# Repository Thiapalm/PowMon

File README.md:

# (PowMon) Power Monitor Board

<p align=center>

</p>

This is a hobby development board conceived for usage in my home lab. The device monitors both a shunt  voltage drop and bus supply voltage. Programmable calibration value, conversion times, and averaging,  combined with an internal multiplier, enable direct readouts of current in amperes and power in watts.

The board has 2 headers used for address configuration, allowing all 16 addresses to be used as you see fit. The board power is provided by the I²C connector, and it can be used in 5V or 3V3 modes. 

## License and certification

This is an open source hardware project licensed under CERN-OHL-P. More details on [LICENSE.md](./LICENSE.md).  

## Project

The PCB project was developed in Kicad 9, all necessary project files are available in this repository and can be used freely, according to License.

## Board specifications

The board is based on the [**INA226**](https://www.ti.com/lit/gpn/ina226) from Texas Instruments.  
Board features commonly used in Embedded Systems:
- Measure voltages from 0V up to 36V
- Configurable averaging options
- Reports current, voltage and power
- I²C serial communication (Two Headers for BUS usage)
- LED indicators (LOAD, Board POWER and ALERT)
- 2.7v up to 5v operation voltage from I²C header
- Board Address selector (A0 and A1)

## Board View 

## Board Enclosure 

There is an enclosure made in Freecad 1.0 available on the enclosure folder, it can be used or modified as you see fit. For best results I recommend to print in transparent filament. You will also need 4 M3 x 10mm screws (black with flat head are recommended).  

## Version Revision

V1 - current version  
   - Added two I²C headers so it can be used in a bus
   - Added Address configuration headers
   - Added informational LEDs

## Firmware

There is no specific firmware for this board, but i have a driver (crate) developed in RUST for INA226, see it in [crates.io](https://crates.io/crates/ina226-tp) or you can search the internet for a c/c++ version.

## Contribution

Unless you explicitly state otherwise, any contribution intentionally submitted for inclusion in the work by you, as defined in the CERN-OHL-P license, shall be licensed as above, without any additional terms or conditions.

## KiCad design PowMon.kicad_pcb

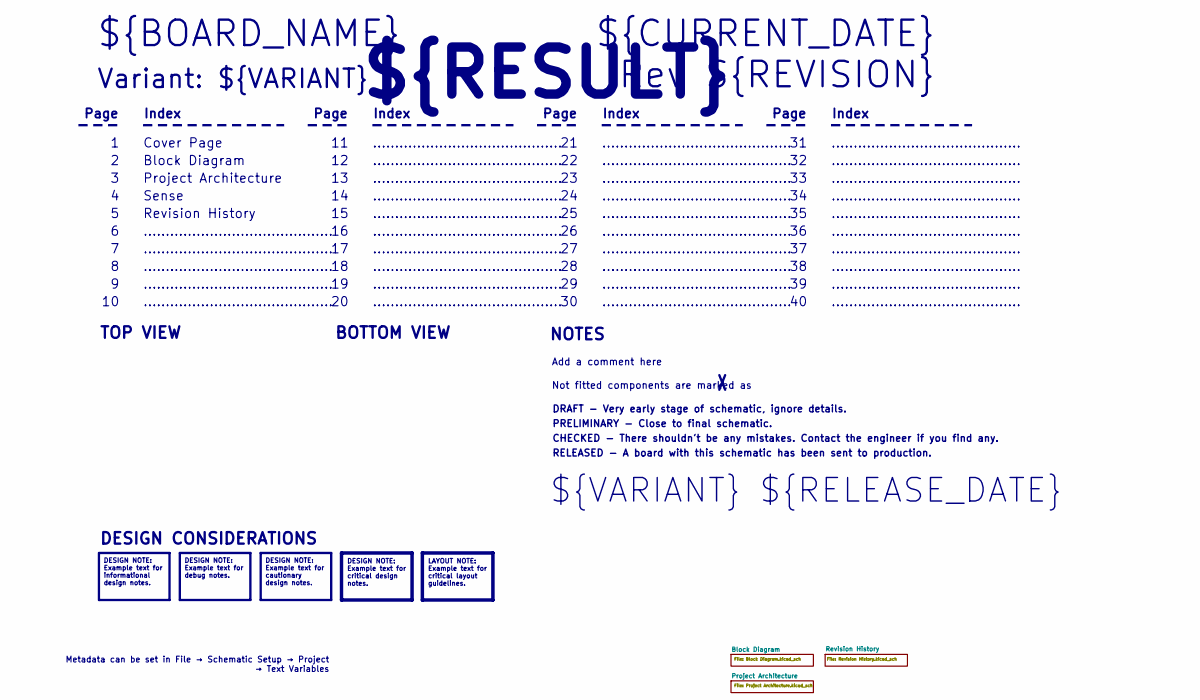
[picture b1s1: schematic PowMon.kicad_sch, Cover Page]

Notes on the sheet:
BOTTOM VIEW
...........................................
RELEASED - A board with this schematic has been sent to production.
Page
TOP VIEW
Not fitted components are marked as
Index
PRELIMINARY - Close to final schematic.
${VARIANT} ${RELEASE_DATE}
Sense
${CURRENT_DATE}
Variant: ${VARIANT}
Rev ${REVISION}
Revision History
${RESULT}
${BOARD_NAME}
DRAFT - Very early stage of schematic, ignore details.
Block Diagram
Add a comment here
Cover Page
NOTES
Project Architecture
CHECKED - There shouldn't be any mistakes. Contact the engineer if you find any.
DESIGN CONSIDERATIONS
Metadata can be set in File → Schematic Setup → Project → Text Variables
DESIGN NOTE: Example text for informational design notes.
LAYOUT NOTE: Example text for critical layout guidelines.
DESIGN NOTE: Example text for cautionary design notes.
DESIGN NOTE: Example text for debug notes.
DESIGN NOTE: Example text for critical design notes.

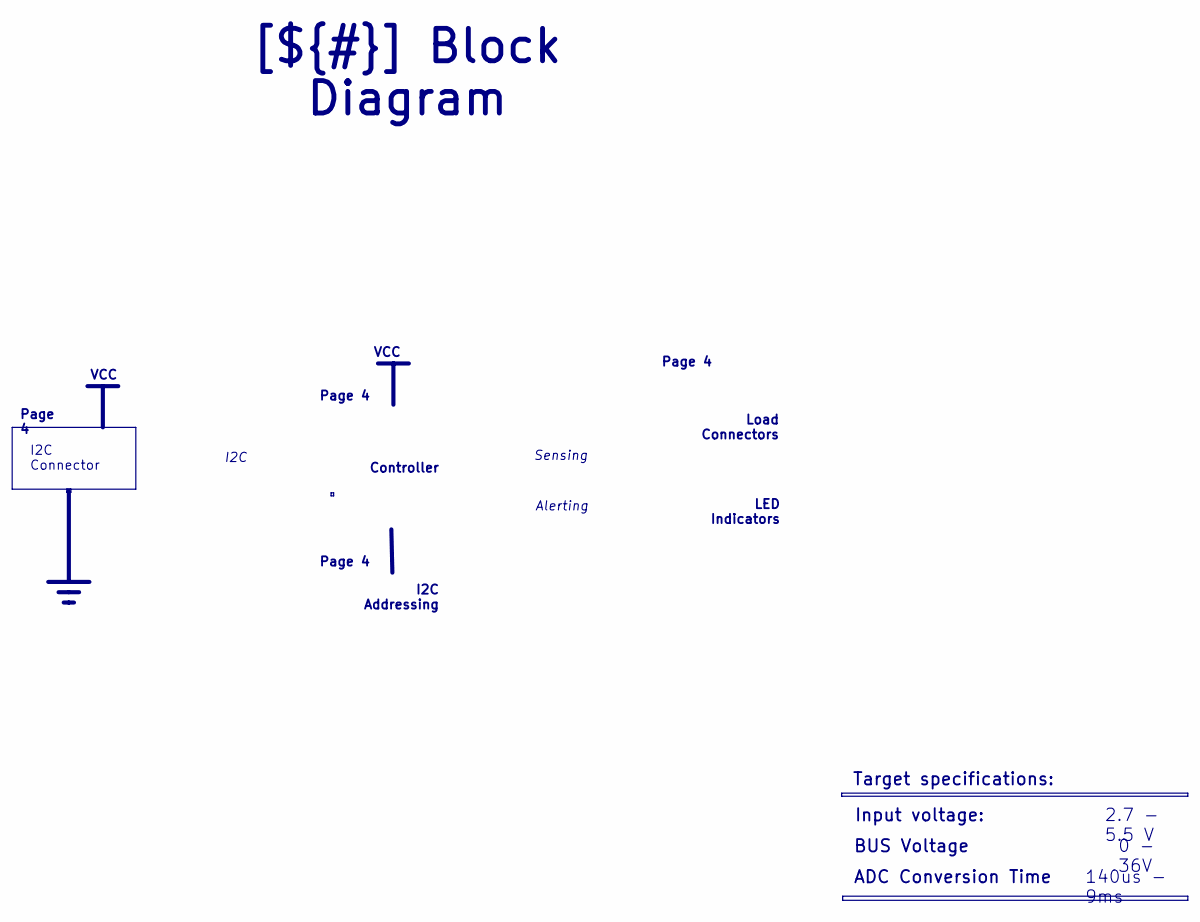
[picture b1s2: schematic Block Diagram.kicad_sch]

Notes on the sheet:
VCC
ADC Conversion Time
BUS Voltage
I2C
Input voltage:
0 - 36V
I2C Addressing
[${#}] ${TITLE}
Page 4
Target specifications:
140us - 9ms
Load Connectors
2.7 - 5.5 V
Sensing
Alerting
LED Indicators
Controller
I2C Connector

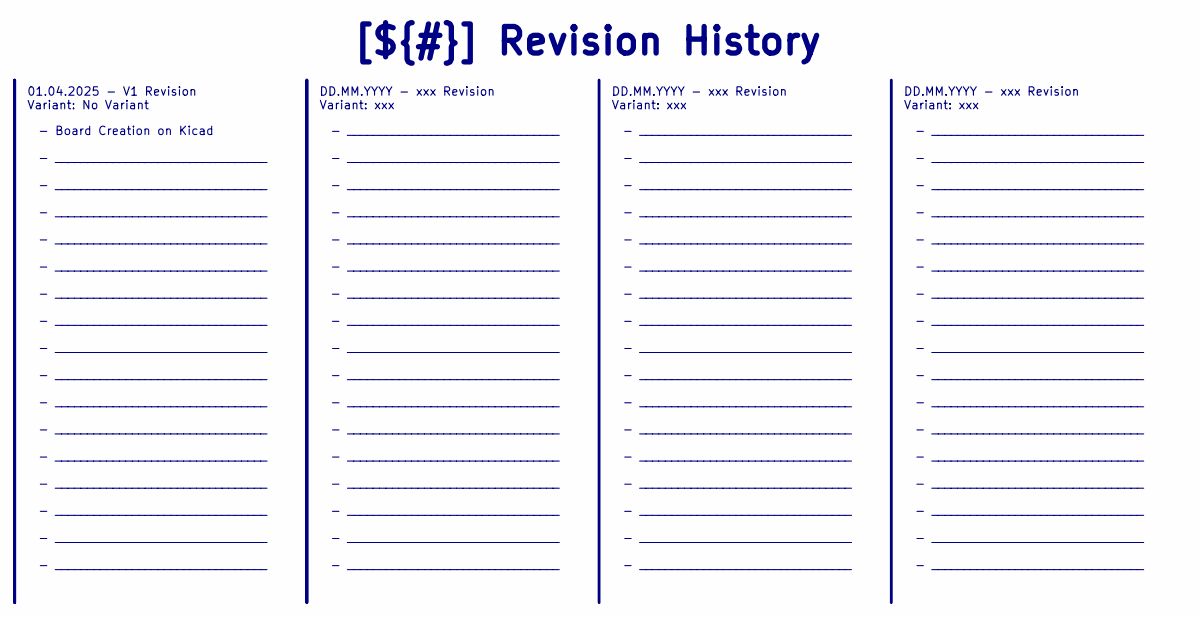
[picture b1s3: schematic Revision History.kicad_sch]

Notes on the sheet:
- _________________________________ - _________________________________ - _________________________________ - _________________________________ - _________________________________ - _________________________________ - _________________________________ - _________________________________ - _________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
DD.MM.YYYY - xxx Revision Variant: xxx
[${#}] ${TITLE}
- Board Creation on Kicad - _________________________________ - _________________________________ - _________________________________ - _________________________________ - _________________________________ - _________________________________ - _________________________________ - ___________________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
01.04.2025 - V1 Revision Variant: No Variant

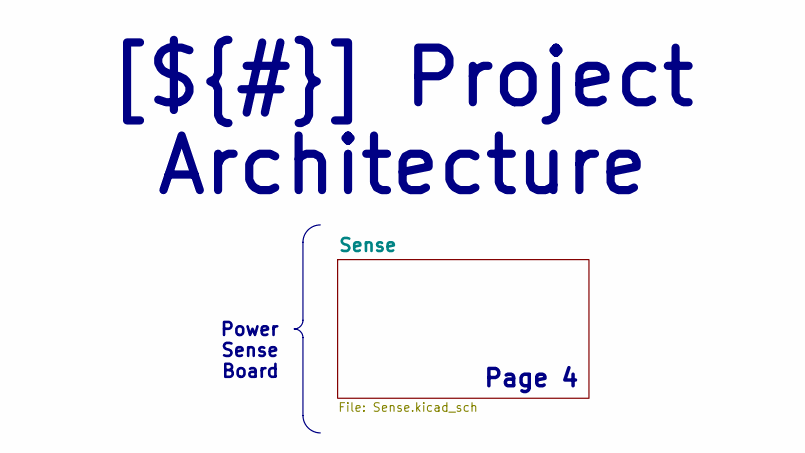
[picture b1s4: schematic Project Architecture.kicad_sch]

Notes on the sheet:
Page 4
Power Sense Board
[${#}] ${TITLE}

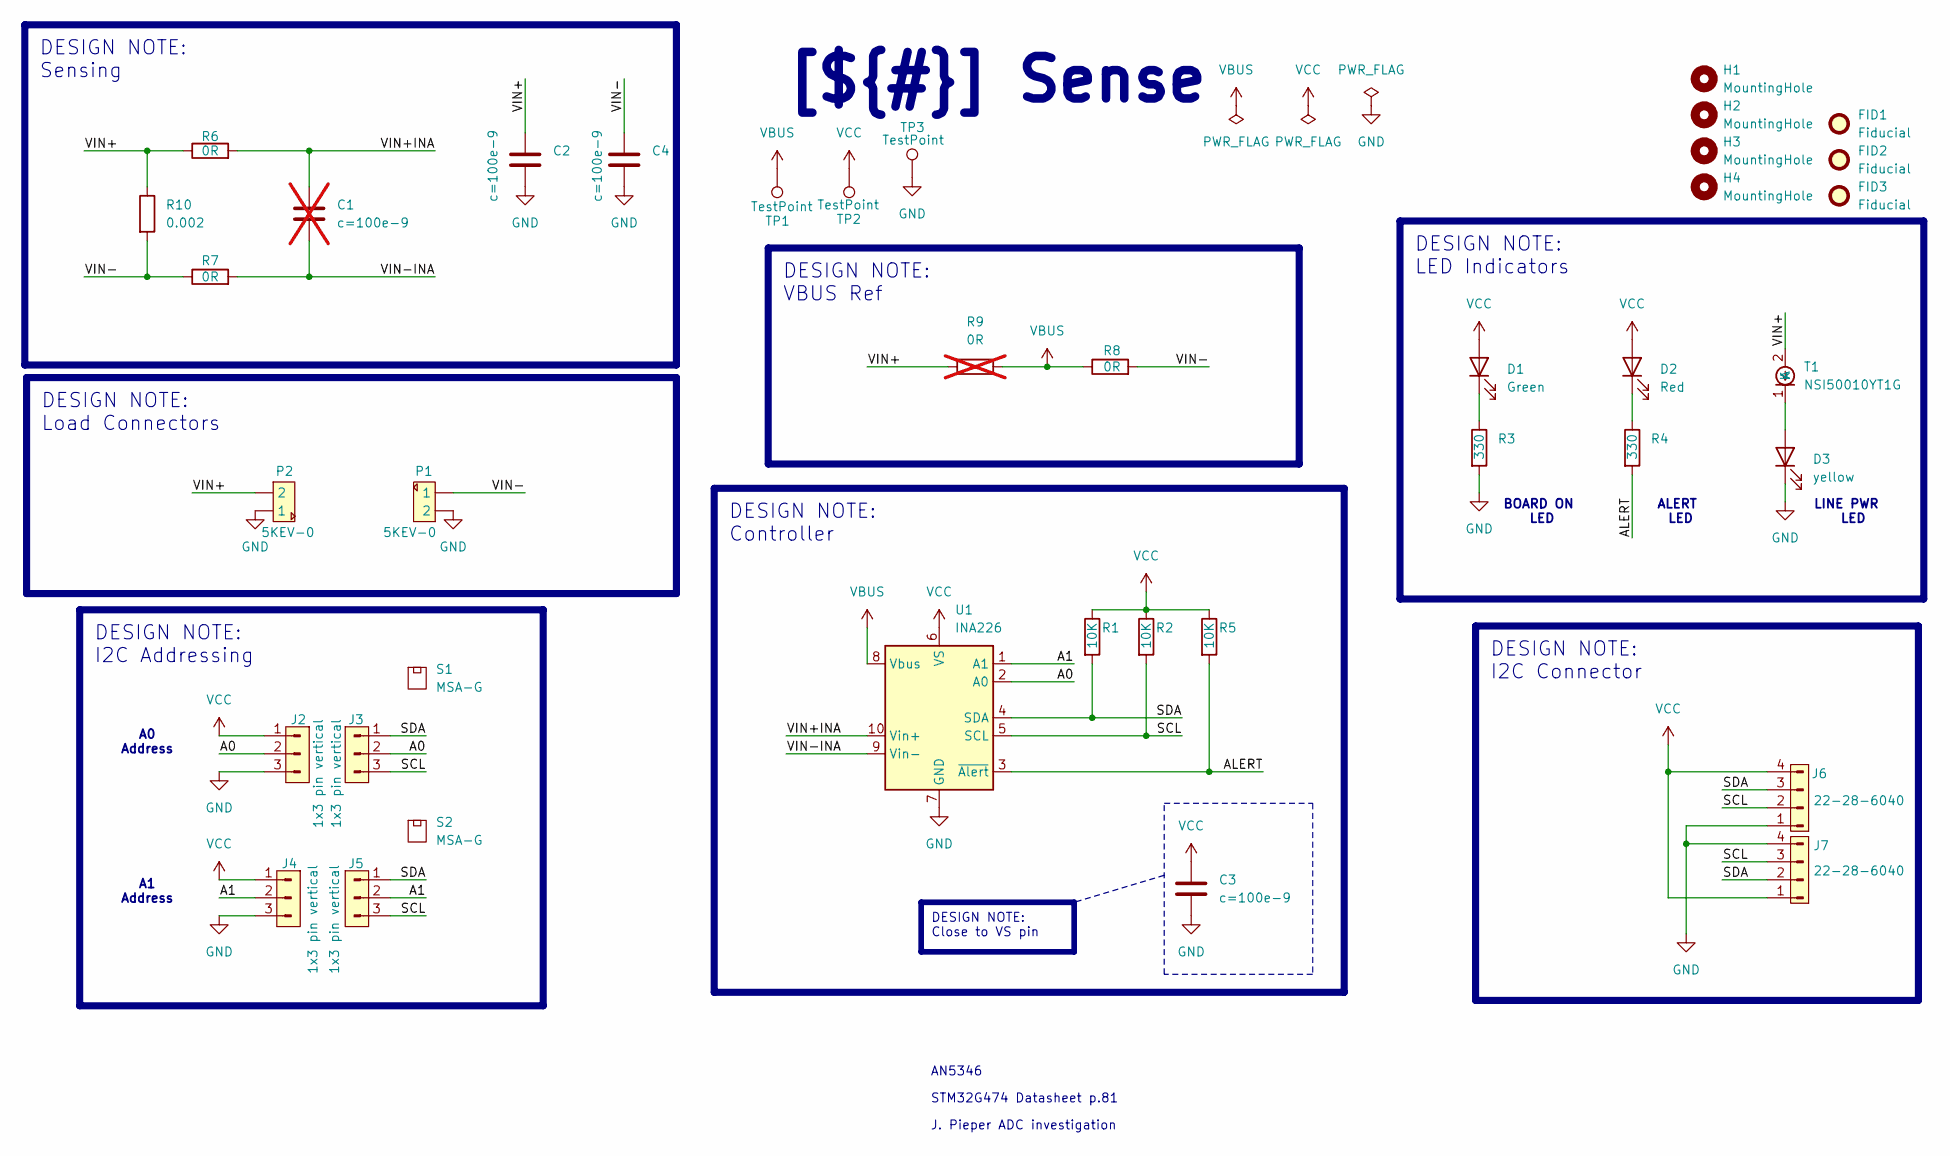
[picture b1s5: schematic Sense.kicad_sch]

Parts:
C1: c=100e-9; C_0805_2012Metric_Pad1.18x1.45mm_HandSolder; Manufacturer Part Number 0805B104K500CT; not fitted
C2, C3, C4: c=100e-9; C_0805_2012Metric_Pad1.18x1.45mm_HandSolder; Manufacturer Part Number 0805B104K500CT
D1: Green; LED_0603_1608Metric; Manufacturer Part Number SML-LX0603GW-TR
D2: Red; LED_0603_1608Metric; Manufacturer Part Number SM0603SRC
D3: yellow; LED_0603_1608Metric; Manufacturer Part Number LTST-C191KSKT
FID1, FID2, FID3: Fiducial; Fiducial_1mm_Mask2mm
H1, H2, H3, H4: MountingHole; MountingHole_3mm
J2, J3, J4, J5: 1x3 pin vertical; PinHeader_1x03_P2.54mm_Vertical; Manufacturer Part Number G800LR305018EU
J6, J7: 22-28-6040; PinHeader_1x04_P2.54mm_Horizontal; Manufacturer Part Number 22-28-6040
P1, P2: 5KEV-0; Terminal Block 5mm; Manufacturer Part Number 5KEV-0
R1, R2, R5: 10K; R_0603_1608Metric_Pad0.98x0.95mm_HandSolder; Manufacturer Part Number CRCW060333R0FKEA
R3, R4: 330; R_0603_1608Metric_Pad0.98x0.95mm_HandSolder; Manufacturer Part Number ERJ-3GEYJ331V
R6, R7, R8: 0R; R_0603_1608Metric_Pad0.98x0.95mm_HandSolder; Manufacturer Part Number CRCW06030000Z0EI
R9: 0R; R_0603_1608Metric_Pad0.98x0.95mm_HandSolder; Manufacturer Part Number CRCW06030000Z0EI; not fitted
R10: 0.002; R_1206_3216Metric_Pad1.30x1.75mm_HandSolder; Manufacturer Part Number WSL12062L000FEA
S1, S2: MSA-G; Manufacturer Part Number MSA-G
T1: NSI50010YT1G; D_SOD-123; Manufacturer Part Number NSI50010YT1G
TP1, TP2, TP3: TestPoint; TestPoint_PTH_1mm_2mm
U1: INA226; VSSOP-10_3x3mm_P0.5mm; Manufacturer Part Number INA226AIDGST

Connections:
/Project Architecture/Sense/A0: J2.2, J3.2, U1.2 (A0)
/Project Architecture/Sense/A1: J4.2, J5.2, U1.1 (A1)
/Project Architecture/Sense/ALERT: R4.2, R5.2, U1.3 (~Alert)
/Project Architecture/Sense/SCL: J3.3, J5.3, J6.2, J7.3, R2.2, U1.5 (SCL)
/Project Architecture/Sense/SDA: J3.1, J5.1, J6.3, J7.2, R1.2, U1.4 (SDA)
/Project Architecture/Sense/VIN+: C2.1, P2.2, R6.1, R9.1, R10.1, T1.2 (A)
/Project Architecture/Sense/VIN+INA: C1.2, R6.2, U1.10 (Vin+)
/Project Architecture/Sense/VIN-: C4.1, P1.1, R7.1, R8.2, R10.2
/Project Architecture/Sense/VIN-INA: C1.1, R7.2, U1.9 (Vin-)
GND: C2.2, C3.1, C4.2, D3.1 (K), J2.3, J4.3, J6.1, J7.4, P1.2, P2.1, R3.2, TP3.1, U1.7 (GND)
unnamed: D1.1 (K), R3.1
unnamed: D2.1 (K), R4.1
unnamed: D3.2 (A), T1.1 (K)
VBUS: R8.1, R9.2, TP1.1, U1.8 (Vbus)
VCC: C3.2, D1.2 (A), D2.2 (A), J2.1, J4.1, J6.4, J7.1, R1.1, R2.1, R5.1, TP2.1, U1.6 (VS)

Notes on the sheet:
A0 Address
ALERT LED
BOARD ON LED
J. Pieper ADC investigation
A1 Address
STM32G474 Datasheet p.81
AN5346
LINE PWR LED
DESIGN NOTE: LED Indicators
DESIGN NOTE: I2C Connector
DESIGN NOTE: Controller
DESIGN NOTE: I2C Addressing
[${#}] ${TITLE}
DESIGN NOTE: Load Connectors
DESIGN NOTE: VBUS Ref
DESIGN NOTE: Close to VS pin
DESIGN NOTE: Sensing

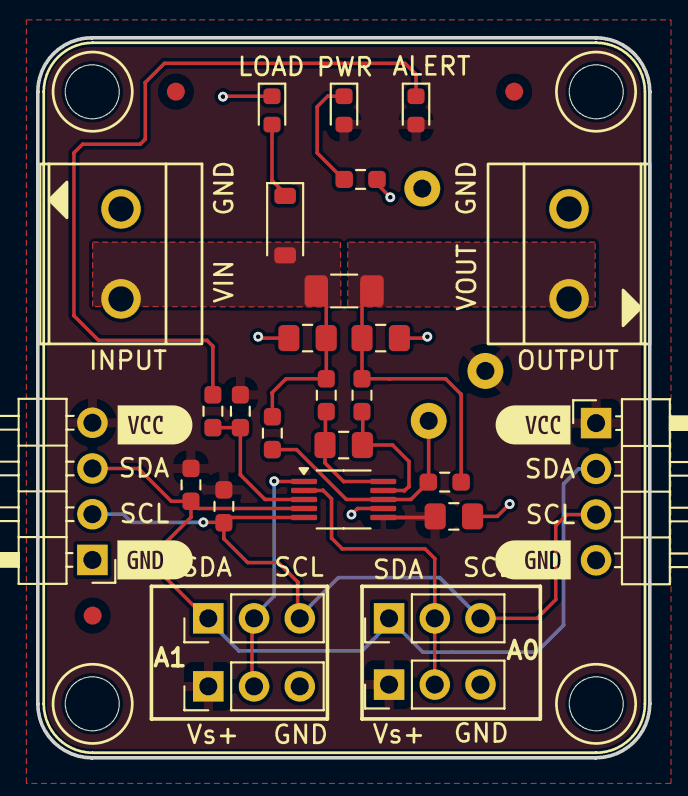
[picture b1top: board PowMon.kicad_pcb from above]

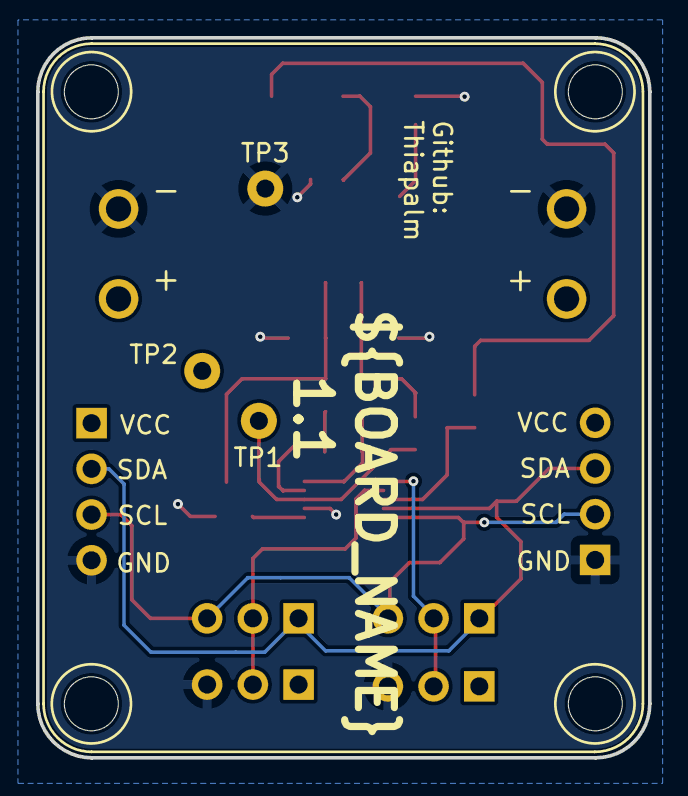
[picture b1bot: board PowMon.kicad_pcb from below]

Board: 2 copper layers, 34.0 x 40.0 mm, 41 parts (3 on the bottom side), 15 nets.

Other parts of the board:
kibuzzard-67FD642C: G***; kibuzzard-67FD642C
kibuzzard-67FD645D: G***; kibuzzard-67FD645D
kibuzzard-67FD646E: G***; kibuzzard-67FD646E
kibuzzard-67FD6413: G***; kibuzzard-67FD6413

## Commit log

2025-03-31 Changed sense resistor and fixed connector position
2025-03-31 Changed resistor position
2025-04-01 Split I2C connector
2025-04-01 Outputs generated, ready for prototyping
2025-04-07 fixed component positions
2025-04-07 Fixed file names
2025-04-08 Added FreeCad made enclosure
2025-08-29 Intermediary save

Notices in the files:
README.md:
License: CERN OHL P
